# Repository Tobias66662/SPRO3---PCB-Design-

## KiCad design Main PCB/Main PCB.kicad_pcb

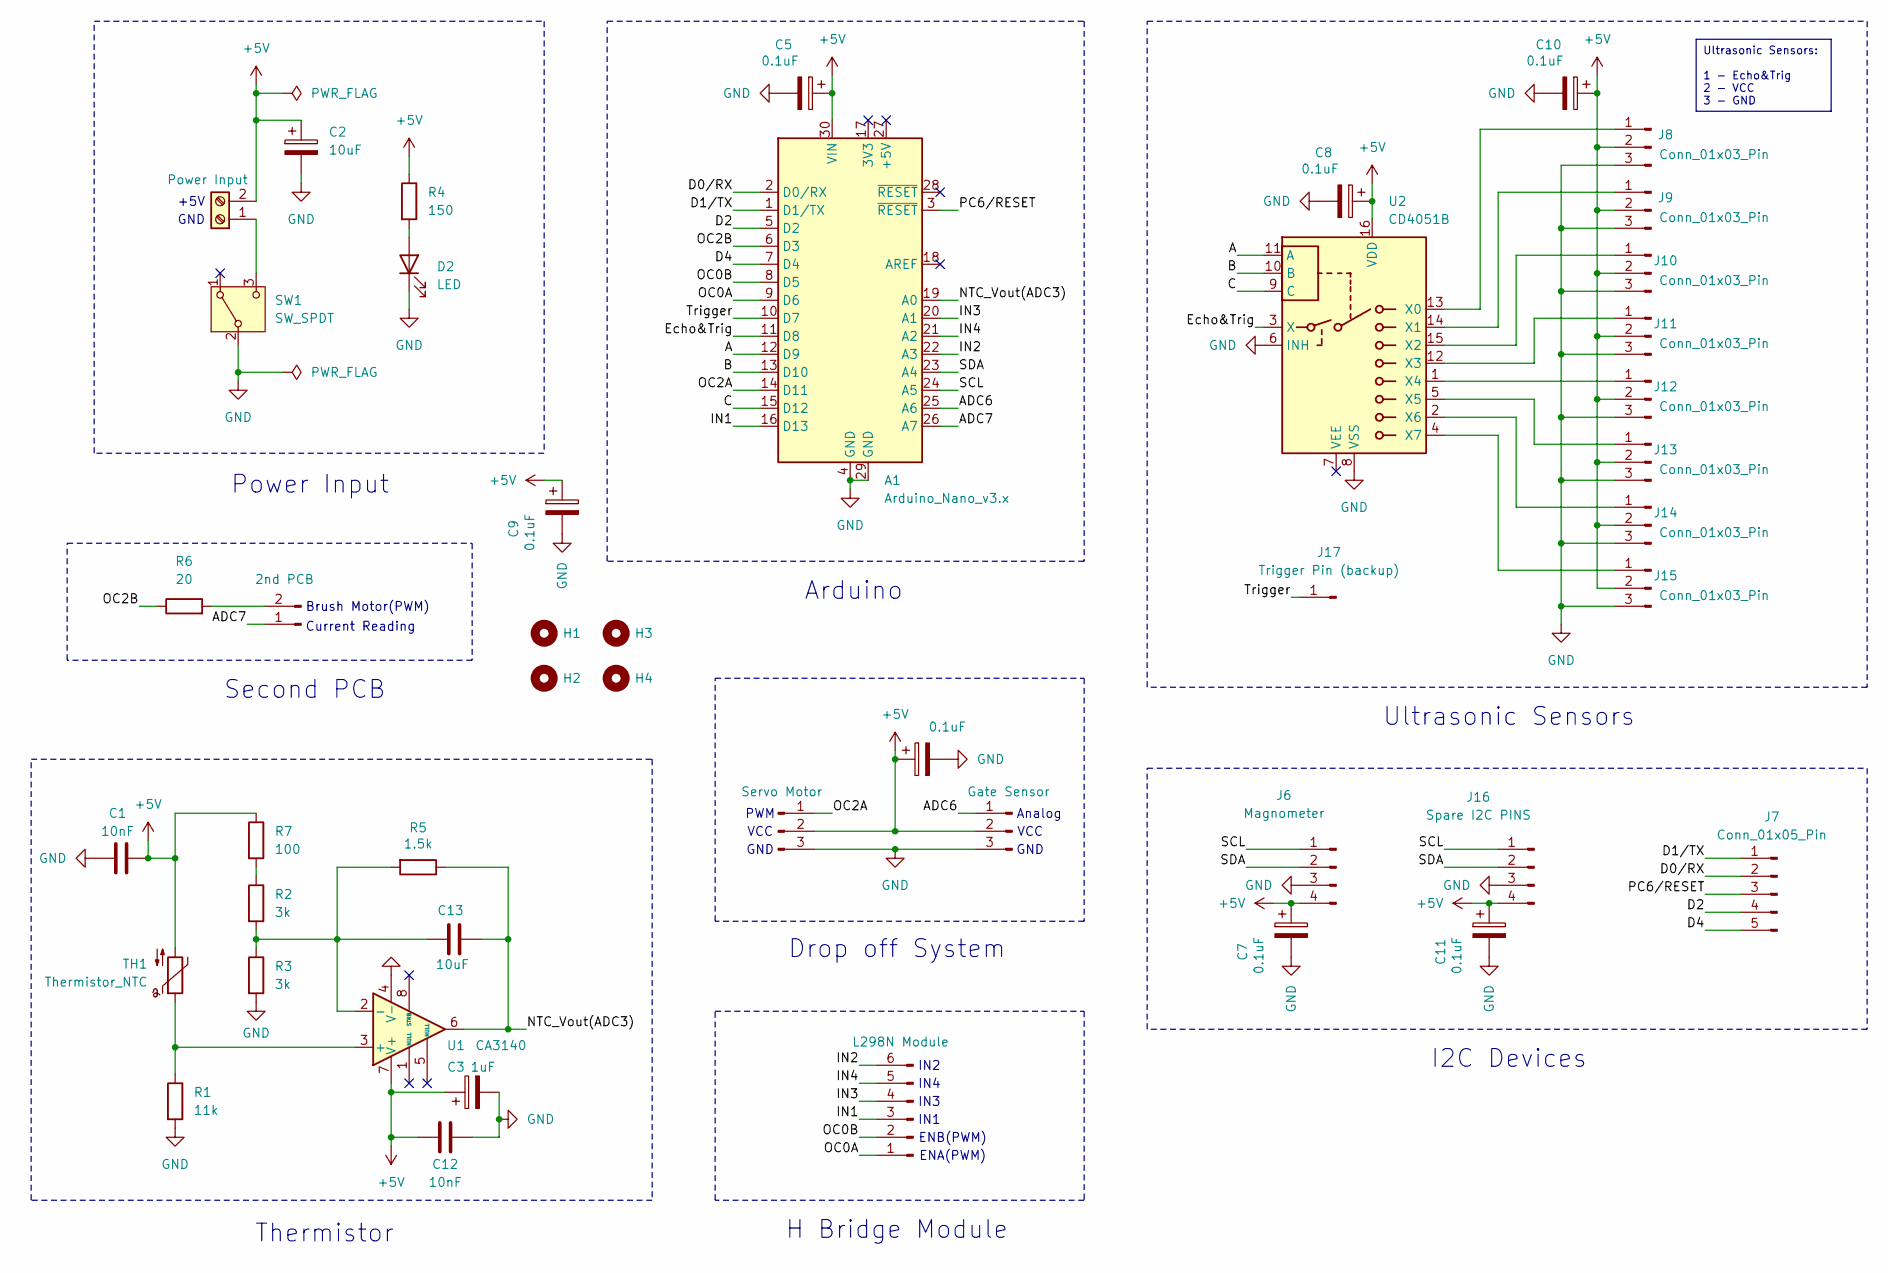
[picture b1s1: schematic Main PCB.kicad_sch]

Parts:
A1: Arduino_Nano_v3.x; Arduino_Nano
C1, C12: 10nF; C_Disc_D3.8mm_W2.6mm_P2.50mm
C2: 10uF; CP_Radial_D5.0mm_P2.50mm
C3: 1uF; CP_Radial_D5.0mm_P2.50mm
C5, C6, C7, C8, C9, C10, C11: 0.1uF; CP_Radial_D5.0mm_P2.50mm
C13: 10uF; C_Disc_D5.0mm_W2.5mm_P5.00mm
D2: LED; LED_D5.0mm
H1, H2, H3, H4: MountingHole; MountingHole_3.2mm_M3
J1: Power Input; TerminalBlock_bornier-2_P5.08mm
J2: 2nd PCB; PinHeader_1x02_P2.54mm_Vertical
J3: Servo Motor; PinHeader_1x03_P2.54mm_Vertical
J4: L298N Module; PinHeader_1x06_P2.54mm_Vertical
J5: Gate Sensor; PinHeader_1x03_P2.54mm_Vertical
J6: Magnometer; PinHeader_1x04_P2.54mm_Vertical
J7: Conn_01x05_Pin; PinHeader_1x05_P2.54mm_Vertical
J8, J9, J10, J11, J12, J13, J14, J15: Conn_01x03_Pin; PinHeader_1x03_P2.54mm_Vertical
J16: Spare I2C PINS; PinHeader_1x04_P2.54mm_Vertical
J17: Trigger Pin (backup); PinHeader_1x01_P2.54mm_Vertical
R1: 11k; R_Axial_DIN0207_L6.3mm_D2.5mm_P10.16mm_Horizontal
R2, R3: 3k; R_Axial_DIN0207_L6.3mm_D2.5mm_P10.16mm_Horizontal
R4: 150; R_Axial_DIN0207_L6.3mm_D2.5mm_P10.16mm_Horizontal
R5: 1.5k; R_Axial_DIN0207_L6.3mm_D2.5mm_P10.16mm_Horizontal
R6: 20; R_Axial_DIN0207_L6.3mm_D2.5mm_P7.62mm_Horizontal
R7: 100; R_Axial_DIN0207_L6.3mm_D2.5mm_P10.16mm_Horizontal
SW1: SW_SPDT; SolderWire-0.75sqmm_1x03_P4.8mm_D1.25mm_OD2.3mm
TH1: Thermistor_NTC; R_Axial_DIN0204_L3.6mm_D1.6mm_P2.54mm_Vertical
U1: CA3140; DIP-8_W7.62mm
U2: CD4051B; DIP-16_W7.62mm

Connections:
+5V: A1.30 (VIN), C1.2, C2.1, C3.1, C5.1, C6.1, C7.1, C8.1, C9.1, C10.1, C11.1, C12.1, J1.2, J3.2, J5.2, J6.4, J8.2, J9.2, J10.2, J11.2, J12.2, J13.2, J14.2, J15.2, J16.4, R4.1, R7.1, TH1.2, U1.7 (V+), U2.16 (VDD)
/A: A1.12 (D9), U2.11 (A)
/ADC6: A1.25 (A6), J5.1
/ADC7: A1.26 (A7), J2.1
/B: A1.13 (D10), U2.10 (B)
/C: A1.15 (D12), U2.9 (C)
/D0/RX: A1.2 (D0/RX), J7.2
/D1/TX: A1.1 (D1/TX), J7.1
/D2: A1.5 (D2), J7.4
/D4: A1.7 (D4), J7.5
/Echo&Trig: A1.11 (D8), U2.3 (X)
/IN1: A1.16 (D13), J4.3
/IN2: A1.22 (A3), J4.6
/IN3: A1.20 (A1), J4.4
/IN4: A1.21 (A2), J4.5
/NTC_Vout(ADC3): A1.19 (A0), C13.1, R5.1, U1.6
/OC0A: A1.9 (D6), J4.1
/OC0B: A1.8 (D5), J4.2
/OC2A: A1.14 (D11), J3.1
/OC2B: A1.6 (D3), R6.1
/PC6/RESET: A1.3 (~RESET), J7.3
/SCL: A1.24 (A5), J6.1, J16.1
/SDA: A1.23 (A4), J6.2, J16.2
/Trigger: A1.10 (D7), J17.1
GND: A1.4 (GND), A1.29 (GND), C1.1, C2.2, C3.2, C5.2, C6.2, C7.2, C8.2, C9.2, C10.2, C11.2, C12.2, D2.1 (K), J3.3, J5.3, J6.3, J8.3, J9.3, J10.3, J11.3, J12.3, J13.3, J14.3, J15.3, J16.3, R1.2, R3.2, SW1.2 (B), U1.4 (V-), U2.6 (INH), U2.8 (VSS)
unnamed: D2.2 (A), R4.2
unnamed: J1.1, SW1.3 (C)
unnamed: J2.2, R6.2
unnamed: J8.1, U2.13 (X0)
unnamed: J9.1, U2.14 (X1)
unnamed: J10.1, U2.15 (X2)
unnamed: J11.1, U2.12 (X3)
unnamed: J12.1, U2.1 (X4)
unnamed: J13.1, U2.5 (X5)
unnamed: J14.1, U2.2 (X6)
unnamed: J15.1, U2.4 (X7)
unnamed: R2.1, R7.2
unnamed: R1.1, TH1.1, U1.3 (+)
unnamed: C13.2, R2.2, R3.1, R5.2, U1.2 (-)

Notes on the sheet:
Ultrasonic Sensors: 1 - Echo&Trig 2 - VCC 3 - GND
GND
VCC
Arduino
Brush Motor(PWM)
IN1
Current Reading
I2C Devices
PWM
Analog
Drop off System
Second PCB
ENA(PWM)
ENB(PWM)
IN3
Thermistor
Power Input
Ultrasonic Sensors
+5V
IN2
H Bridge Module
IN4

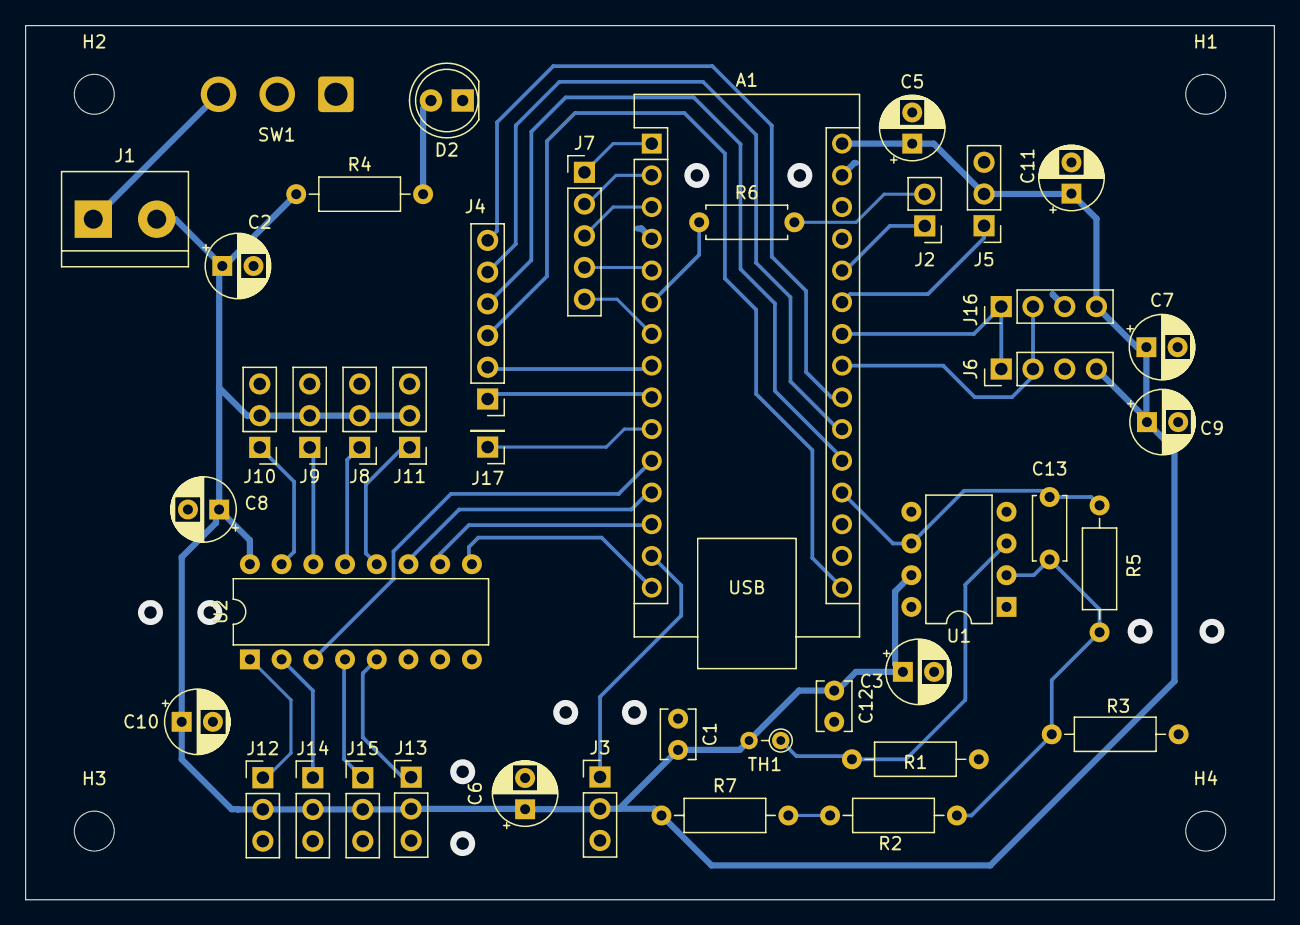
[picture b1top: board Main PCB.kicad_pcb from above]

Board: 2 copper layers, 100.0 x 70.0 mm, 46 parts (0 on the bottom side), 39 nets.

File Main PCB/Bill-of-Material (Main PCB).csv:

"Reference","Value","Datasheet","Footprint","Qty","DNP"
"A1","Arduino_Nano_v3.x","http://www.mouser.com/pdfdocs/Gravitech_Arduino_Nano3_0.pdf","Module:Arduino_Nano","1",""
"C1,C12","10nF","~","Capacitor_THT:C_Disc_D3.8mm_W2.6mm_P2.50mm","2",""
"C2","10uF","~","Capacitor_THT:CP_Radial_D5.0mm_P2.50mm","1",""
"C3","1uF","~","Capacitor_THT:CP_Radial_D5.0mm_P2.50mm","1",""
"C4,C13","47uF","https://docs.rs-online.com/8182/0900766b81302b8d.pdf","Capacitor_THT:CP_Radial_D6.3mm_P2.50mm","2",""
"C5,C6,C7,C8,C9,C10,C11","0.1uF","~","Capacitor_THT:CP_Radial_D5.0mm_P2.50mm","7",""
"D2","LED","~","LED_THT:LED_D5.0mm","1",""
"J1","Power Input","https://docs.rs-online.com/0623/0900766b8157c7d5.pdf","TerminalBlock:TerminalBlock_bornier-2_P5.08mm","1",""
"J2","2nd PCB","~","Connector_PinHeader_2.54mm:PinHeader_1x02_P2.54mm_Vertical","1",""
"J3","Servo Motor","https://docs.rs-online.com/870b/0900766b8123f8a1.pdf","Connector_PinHeader_2.54mm:PinHeader_1x03_P2.54mm_Vertical","1",""
"J4","L298N Module","https://www.sparkfun.com/datasheets/Robotics/L298_H_Bridge.pdf","Connector_PinHeader_2.54mm:PinHeader_1x06_P2.54mm_Vertical","1",""
"J5","Gate Sensor","~","Connector_PinHeader_2.54mm:PinHeader_1x03_P2.54mm_Vertical","1",""
"J6","Magnometer","https://digilent.com/reference/_media/reference/pmod/pmodcmp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","Connector_PinHeader_2.54mm:PinHeader_1x04_P2.54mm_Vertical","1",""
"J7","GPS Module","~https://cdn-learn.adafruit.com/downloads/pdf/adafruit-ultima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","Connector_PinSocket_2.54mm:PinSocket_1x04_P2.54mm_Vertical","1",""
"J8,J9,J10,J11,J12,J13,J14,J15","Conn_01x03_Pin","~","Connector_PinHeader_2.54mm:PinHeader_1x03_P2.54mm_Vertical","8",""
"J16","Spare I2C PINS","~","Connector_PinHeader_2.54mm:PinHeader_1x04_P2.54mm_Vertical","1",""
"J17","Trigger Pin (backup)","~","Connector_PinHeader_2.54mm:PinHeader_1x01_P2.54mm_Vertical","1",""
"R1","11k","~","Resistor_THT:R_Axial_DIN0207_L6.3mm_D2.5mm_P10.16mm_Horizontal","1",""
"R2,R3","3k","~","Resistor_THT:R_Axial_DIN0207_L6.3mm_D2.5mm_P10.16mm_Horizontal","2",""
"R4","150","~","Resistor_THT:R_Axial_DIN0207_L6.3mm_D2.5mm_P10.16mm_Horizontal","1",""
"R5","1.5k","~","Resistor_THT:R_Axial_DIN0207_L6.3mm_D2.5mm_P10.16mm_Horizontal","1",""
"R6","20","~","Resistor_THT:R_Axial_DIN0207_L6.3mm_D2.5mm_P7.62mm_Horizontal","1",""
"R7","100","~","Resistor_THT:R_Axial_DIN0207_L6.3mm_D2.5mm_P10.16mm_Horizontal","1",""
"SW1","SW_SPDT","https://docs.rs-online.com/6e6f/0900766b81587662.pdf","Connector_Wire:SolderWire-0.75sqmm_1x03_P4.8mm_D1.25mm_OD2.3mm","1",""
"TH1","Thermistor_NTC","https://www.digikey.com/en/htmldatasheets/production/666878/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","Resistor_THT:R_Axial_DIN0204_L3.6mm_D1.6mm_P2.54mm_Vertical","1",""
"U1","CA3140","https://www.renesas.com/en/document/dst/ca3140-ca3140a-datasheet","Package_DIP:DIP-8_W7.62mm","1",""
"U2","CD4051B","http://www.ti.com/lit/ds/symlink/cd4052b.pdf","Package_DIP:DIP-16_W7.62mm","1",""

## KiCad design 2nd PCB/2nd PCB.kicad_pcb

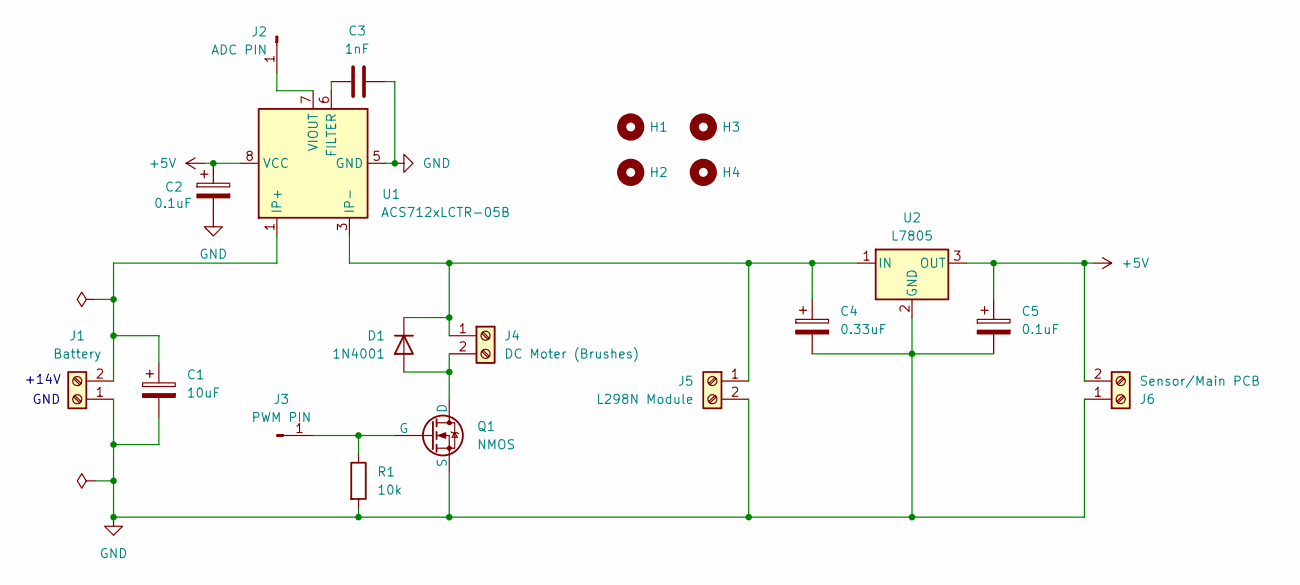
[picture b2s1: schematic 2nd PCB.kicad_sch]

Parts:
C1: 10uF; CP_Radial_D5.0mm_P2.50mm
C2, C5: 0.1uF; CP_Radial_D5.0mm_P2.50mm
C3: 1nF; C_Disc_D3.0mm_W2.0mm_P2.50mm
C4: 0.33uF; CP_Radial_D5.0mm_P2.50mm
D1: 1N4001; D_DO-41_SOD81_P10.16mm_Horizontal
H1, H2, H3, H4: MountingHole; MountingHole_3.2mm_M3
J1: Battery; TerminalBlock_bornier-2_P5.08mm
J2: ADC PIN; PinHeader_1x01_P2.54mm_Vertical
J3: PWM PIN; PinHeader_1x01_P2.54mm_Vertical
J4: DC Moter (Brushes); TerminalBlock_bornier-2_P5.08mm
J5: L298N Module; TerminalBlock_bornier-2_P5.08mm
J6: Sensor/Main PCB; TerminalBlock_bornier-2_P5.08mm
Q1: NMOS; TO-220-3_Vertical
R1: 10k; R_Axial_DIN0207_L6.3mm_D2.5mm_P10.16mm_Horizontal
U1: ACS712xLCTR-05B; SOIC-8_3.9x4.9mm_P1.27mm
U2: L7805; TO-220-3_Vertical

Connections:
+5V: C2.1, C5.1, J6.2, U1.8 (VCC), U2.3 (OUT)
GND: C1.2, C2.2, C3.1, C4.2, C5.2, J1.1, J5.2, J6.1, Q1.3 (S), R1.2, U1.5 (GND), U2.2 (GND)
unnamed: D1.2 (A), J4.2, Q1.1 (D)
unnamed: C4.1, D1.1 (K), J4.1, J5.1, U1.3 (IP-), U1.4 (IP-), U2.1 (IN)
unnamed: C1.1, J1.2, U1.1 (IP+), U1.2 (IP+)
unnamed: J2.1, U1.7 (VIOUT)
unnamed: J3.1, Q1.2 (G), R1.1
unnamed: C3.2, U1.6 (FILTER)

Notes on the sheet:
GND
+14V

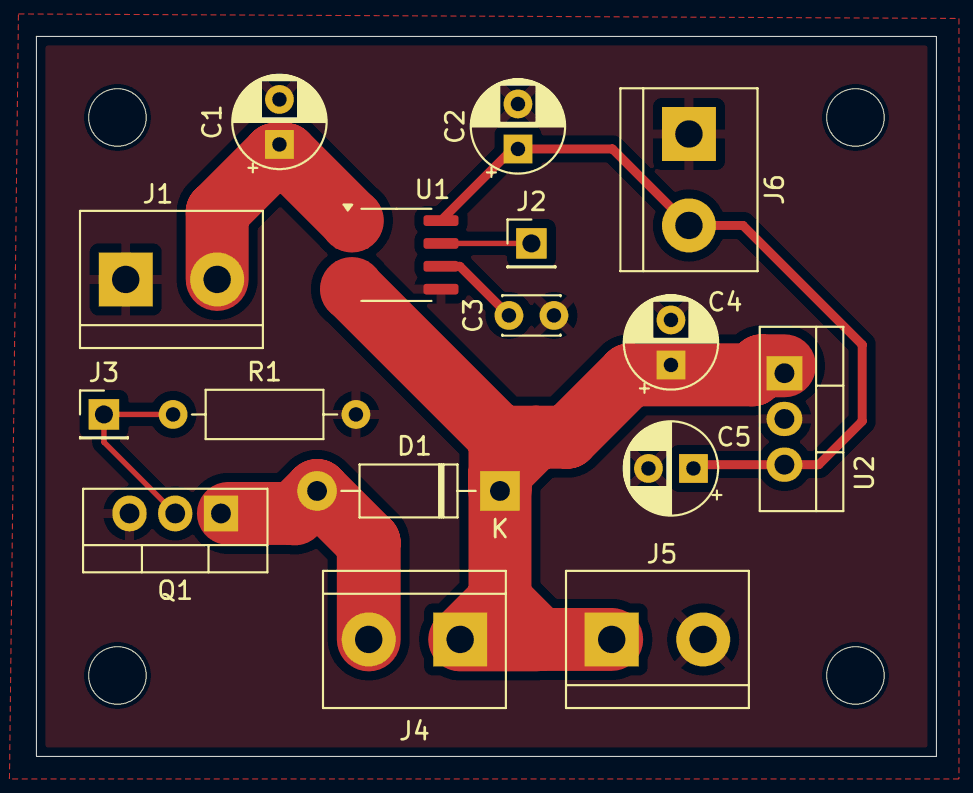
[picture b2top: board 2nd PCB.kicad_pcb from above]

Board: 2 copper layers, 50.0 x 40.0 mm, 20 parts (0 on the bottom side), 8 nets.

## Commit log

2024-11-02 Initaial commit
2024-11-03 added components to the schematic
2024-11-03 Added bypass capacitor to MUX
2024-11-13 udated MUX schematic
2024-11-18 Added Kicad files for the second PCB that we are making
2024-11-18 Added linear voltage regulator to 2nd PCB
2024-11-19 Added labels and pin connections to the main PCB
2024-11-22 Added footnotes to the main PCB and tested and tested stuff in the board editor
2024-11-23 First attempt at designing the board for the second PCB
2024-11-23 First attempt at designing the main PCB board
2024-11-24 Made some edits to the main PCB board
2024-11-25 Added to main PCB board
2024-11-25 finished the PCB board designs
2024-11-27 First iteration of both PCB's send for review
2024-11-27 Removed Main PCB from 2nd PCB folder
2024-12-10 Second revision
2024-12-17 Added manual vias
